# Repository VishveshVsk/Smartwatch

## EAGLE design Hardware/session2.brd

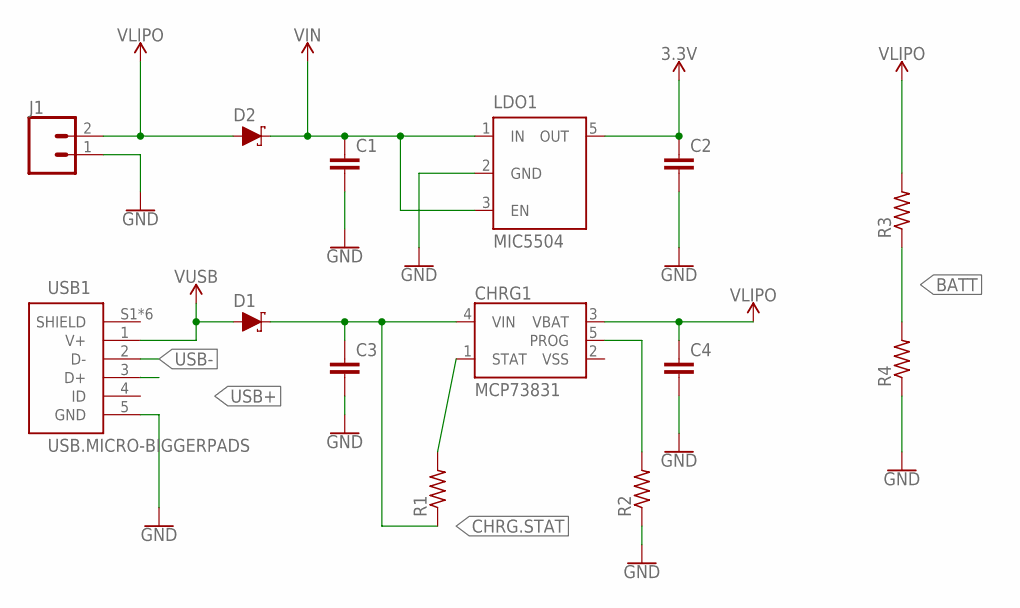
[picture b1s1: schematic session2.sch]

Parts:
C1, C2, C3, C4: CAPACITOR0603; C0603
CHRG1: MCP73831; SOT23-5
D1, D2: SCHOTTKY-USC; USC
J1: CONN_02; 1X02
LDO1: MIC5504; SOT23-5
R1, R2, R3, R4: RESISTOR0603; R0603
USB1: USB.MICRO-BIGGERPADS; USB-MICRO-01.BIGGERPADS

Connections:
3.3V: C2.1, LDO1.5 (OUT)
BATT: R3.1, R4.2
CHRG.STAT: C3.1, CHRG1.4 (VIN), D1.- (C), R1.1
GND: C1.2, C2.2, C3.2, C4.2, J1.1, LDO1.2 (GND), R2.1, R4.1, USB1.5 (GND)
unnamed: CHRG1.1 (STAT), R1.2
unnamed: CHRG1.5 (PROG), R2.2
USB+: USB1.3 (D+)
USB-: USB1.2 (D-)
VIN: C1.1, D2.- (C), LDO1.1 (IN), LDO1.3 (EN)
VLIPO: C4.1, CHRG1.3 (VBAT), D2.+ (A), J1.2, R3.2
VSS: CHRG1.2 (VSS)
V_USB: D1.+ (A), USB1.1 (V+)

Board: 2 copper layers, 14 parts (0 on the bottom side), 9 nets, no tracks yet.

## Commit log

2020-02-08 moved folders around
